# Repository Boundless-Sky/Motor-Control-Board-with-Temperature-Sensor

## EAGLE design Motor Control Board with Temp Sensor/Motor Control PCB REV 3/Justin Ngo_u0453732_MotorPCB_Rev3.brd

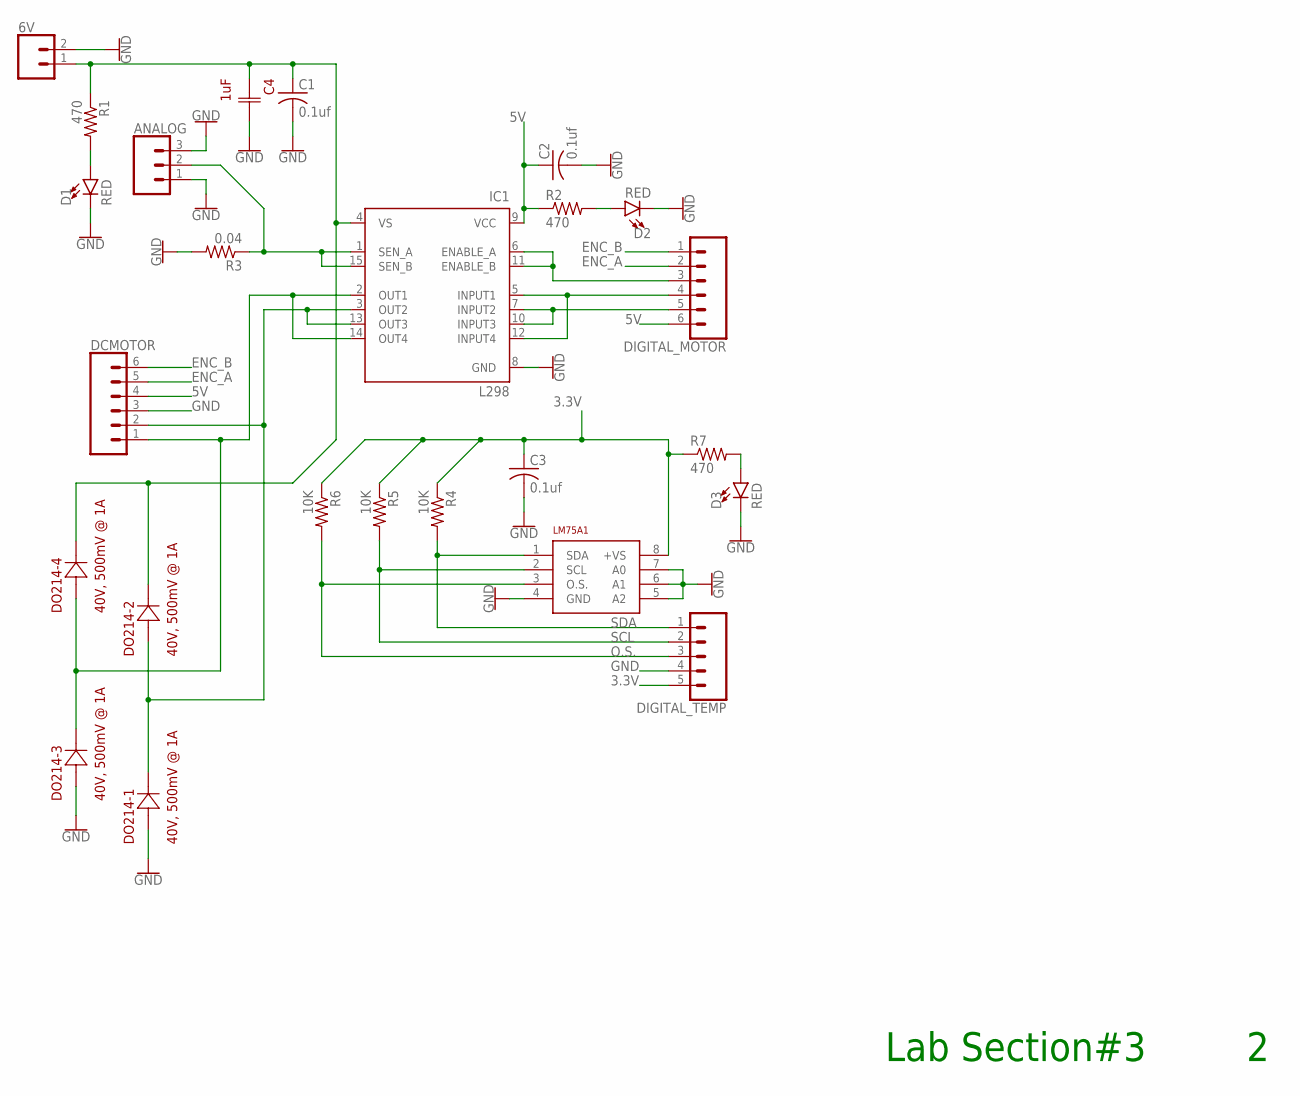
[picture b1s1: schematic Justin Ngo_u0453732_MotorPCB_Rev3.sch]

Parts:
6V: CONN_025MM; SCREWTERMINAL-5MM-2
ANALOG: CONN_03; 1X03
C1, C2, C3: 0.1uf; C1206
C4: 1uF; U1-E
D1, D2, D3: RED; LED-1206
DCMOTOR: CONN_06LOCK_LONGPADS; 1X06_LOCK_LONGPADS
DIGITAL_MOTOR: CONN_06LOCK_LONGPADS; 1X06_LOCK_LONGPADS
DIGITAL_TEMP: CONN_05LOCK_LONGPADS; 1X05_LOCK_LONGPADS
DO214-1, DO214-2, DO214-3, DO214-4: 40V, 500mV @ 1A; DIODE_DO214AC
IC1: L298; MULTIWATT-15
LM75A1: TI-LM75A
R1, R2, R7: 470; R1206
R3: 0.04; R1206
R4, R5, R6: 10K; R1206

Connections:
3.3V: C3.1, DIGITAL_TEMP.5, LM75A1.8 (+VS), R4.1, R5.1, R6.1, R7.1
5V: C2.1, DCMOTOR.4, DIGITAL_MOTOR.6, IC1.9 (VCC), R2.1
ANALOG: ANALOG.2, IC1.1 (SEN_A), IC1.15 (SEN_B), R3.1
ENC_A: DCMOTOR.5, DIGITAL_MOTOR.2
ENC_B: DCMOTOR.6, DIGITAL_MOTOR.1
GND: 6V.2, ANALOG.1, ANALOG.3, C1.2, C2.2, C3.2, C4.2 (22), D1.C, D2.C, D3.C, DCMOTOR.3, DIGITAL_TEMP.4, DO214-1.2 (21), DO214-3.2 (21), IC1.8 (GND), LM75A1.4 (GND), LM75A1.5 (A2), LM75A1.6 (A1), LM75A1.7 (A0), R3.2
unnamed: D1.A, R1.2
unnamed: D3.A, R7.2
unnamed: DIGITAL_MOTOR.3, IC1.6 (ENABLE_A), IC1.11 (ENABLE_B)
unnamed: DIGITAL_MOTOR.5, IC1.7 (INPUT2), IC1.10 (INPUT3)
unnamed: DIGITAL_MOTOR.4, IC1.5 (INPUT1), IC1.12 (INPUT4)
unnamed: DCMOTOR.2, DO214-1.1 (12), DO214-2.2 (21), IC1.3 (OUT2), IC1.13 (OUT3)
unnamed: DCMOTOR.1, DO214-3.1 (12), DO214-4.2 (21), IC1.2 (OUT1), IC1.14 (OUT4)
unnamed: 6V.1, C1.1, C4.1 (11), DO214-2.1 (12), DO214-4.1 (12), IC1.4 (VS), R1.1
unnamed: D2.A, R2.2
O.S.: DIGITAL_TEMP.3, LM75A1.3 (O.S.), R6.2
SCL: DIGITAL_TEMP.2, LM75A1.2 (SCL), R5.2
SDA: DIGITAL_TEMP.1, LM75A1.1 (SDA), R4.2

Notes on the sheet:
Lab Section#3

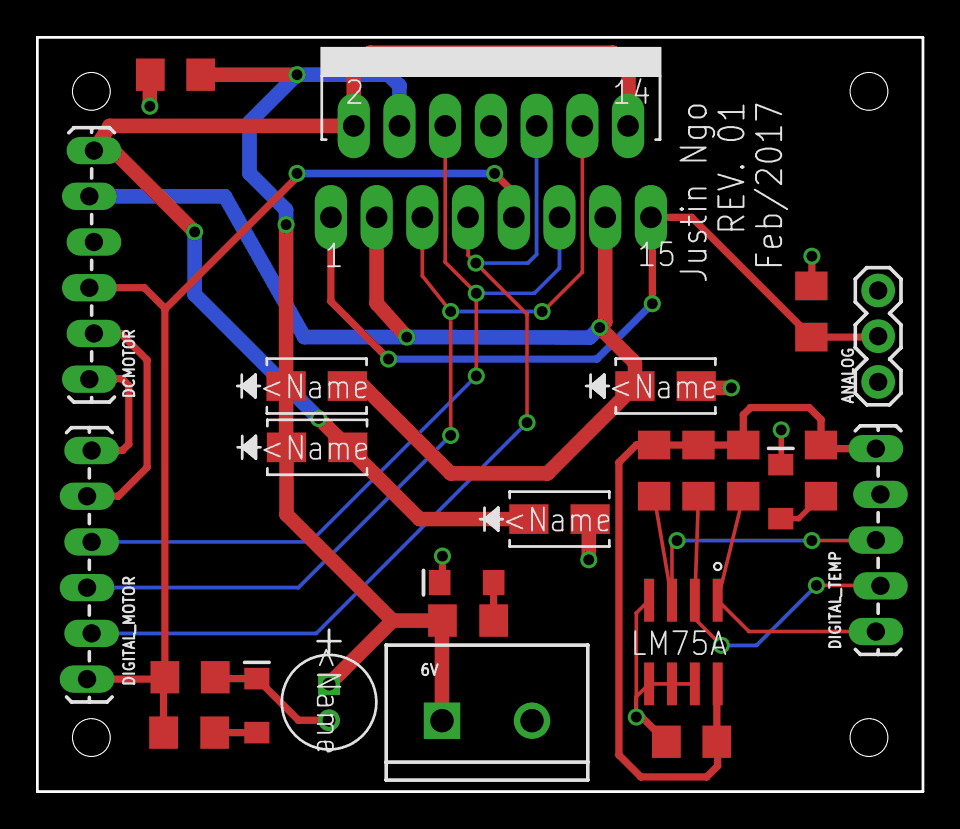
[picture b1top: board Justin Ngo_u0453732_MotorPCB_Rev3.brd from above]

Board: 2 copper layers, 49.2 x 41.9 mm, 25 parts (0 on the bottom side), 18 nets.

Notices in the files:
parts and their libraries:
SparkFun-Connectors: Licensing: Creative Commons ShareAlike 4.0 International - https://creativecommons.org/licenses/by-sa/4.0
COPYRIGHT: Copyright C 2015 Accelerated Designs. All rights reserved
